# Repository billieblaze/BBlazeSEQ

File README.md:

BBlaze-SEQ
==========

Arduino Based Midi Sequencer w/ LCD, Nav Buttons, RGB LED Matrix / Keypad

This is my first Arduino Project, but not my first microcontroller project.   

Platform: 
=========

* SainSmart Arduino Mega 2560 clone
* SainSmart i2c LCD
* MIDI IN / MIDI OUT (6n139)
* MicroChip 24LC256 - 256k RAM 
* SparkFun 4x4 RGB LED / Button Matrix - 74hc595 shift registers for LED - 74hc164/165 for button matrix

* Navigation 
    - using a digital in module from Midibox.org - but again, just some 74hc595
    * 8 rotary encoder / swithces 
    * 5 nav buttons
    * pattern change rotary/encoder

Libraries:
==========

* SainSmart i2c LCD
* ShiftMatrixPWM
* MIDI 
* Timer3 

Roadmap: 
========

* add save / clear / copy pattern
* allow CC data in the pattern
* PCB Design

ChangeLog:
==========

* v0.9 - Split core .ino file into packages (lcd, keypad, matrix, etc) - working on timing (might remove interrupt) and general cleanup of UI handlers
* v0.8 - Added 24LC256 - working on timing of UI routines - added "record+keyboard" mode
* v0.7 - moved the button handling to an interrupt and added "updateLCD" flag which will update on the next loop()
* v0.6 - switch to i2c LCD and arduino mega 2560
* v0.5 - Replace sequence array that come from Cahors / buttons now toggle notes in the array
* v0.4 - Integrate Keypad w/ a Voltage Divider to A5
* v0.3 - Integrate LED Matrix (shiftPWMMatrix + 75hc595)
* v0.2 - LCD / Menu / Nav Buttons / Simple OS   (sainSmart LCD / Keypad)
* v0.1 - basic poc / find libraries

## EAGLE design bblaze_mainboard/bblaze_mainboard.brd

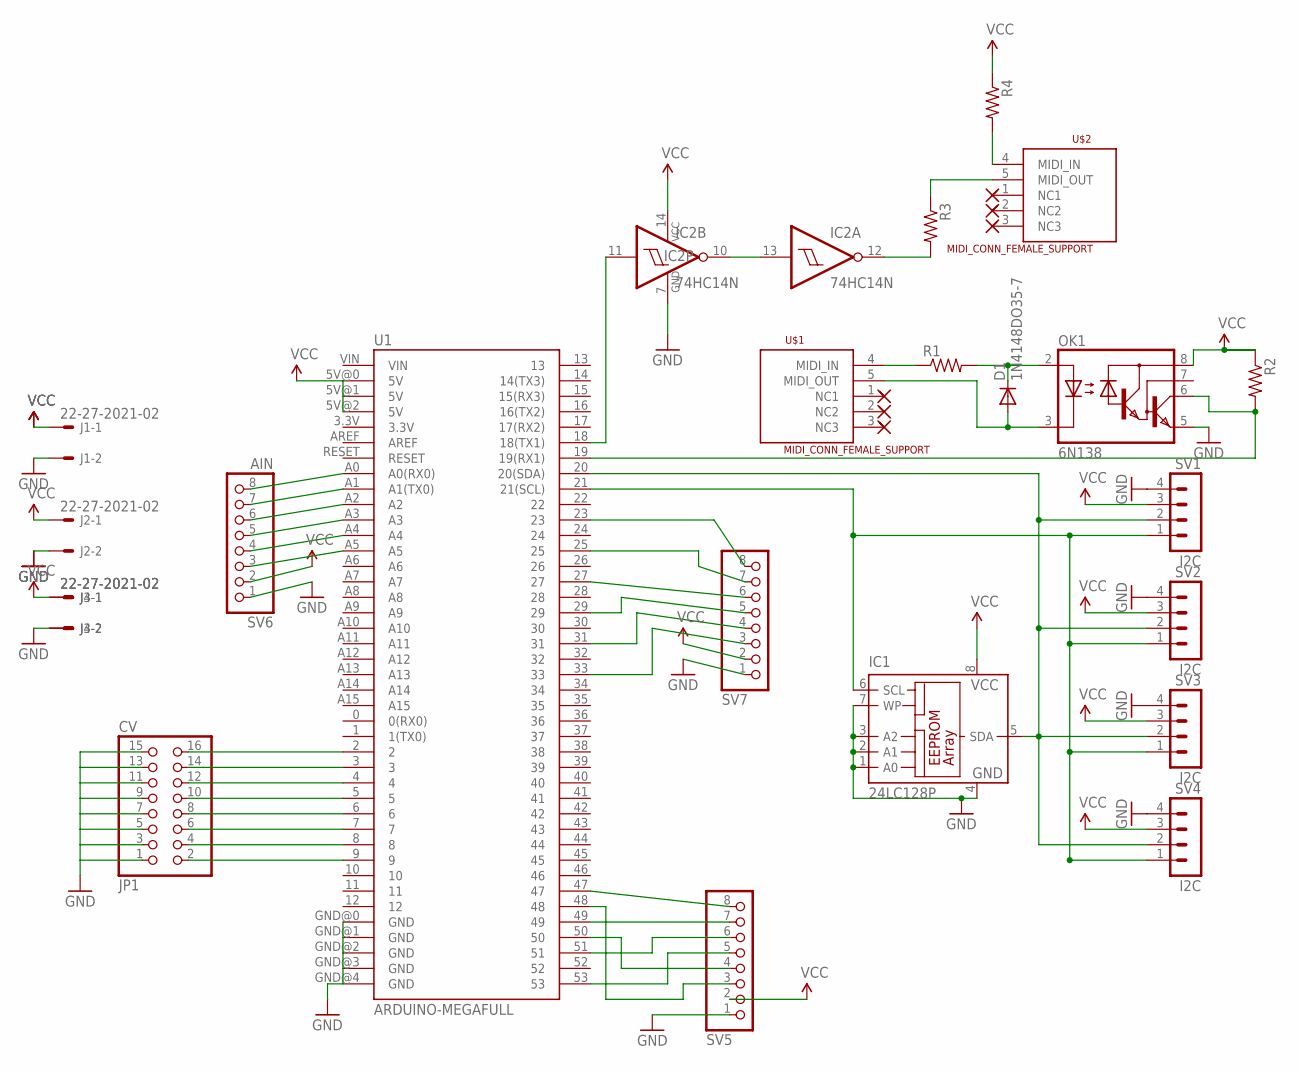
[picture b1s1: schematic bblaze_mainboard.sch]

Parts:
D1: 1N4148DO35-7; DO35-7
IC1: 24LC128P; DIL8
IC2: 74HC14N; DIL14
J1, J2, J3, J4: 22-27-2021-02; 6410-02
JP1: CV; 2X08
OK1: 6N138; DIL08
R1, R2, R3, R4: RESISTORKIT; AXIAL-0.3-KIT
SV1, SV2, SV3, SV4: I2C; MA04-1
SV5, SV7: PINHD-1X8; 1X08
SV6: AIN; 1X08
U1: ARDUINO-MEGAFULL; ARDUINO_MEGA
U$1, U$2: MIDI_CONN_FEMALE_SUPPORT; DIN_5_FEMALE_SUPPORT

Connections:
GND: IC1.1 (A0), IC1.2 (A1), IC1.3 (A2), IC1.4 (GND), IC1.7 (WP), IC2.7 (GND), J1.2, J2.2, J3.2, J4.2, JP1.1, JP1.3, JP1.5, JP1.7, JP1.9, JP1.11, JP1.13, JP1.15, OK1.5 (GND), SV1.4, SV2.4, SV3.4, SV4.4, SV5.1, SV6.1, SV7.1, U1.GND@0 (GND), U1.GND@1 (GND), U1.GND@2 (GND), U1.GND@3 (GND), U1.GND@4 (GND)
unnamed: D1.C, OK1.2 (A), R1.P$2 (2)
unnamed: D1.A, OK1.3 (C), U$1.5 (MIDI_OUT)
unnamed: R1.P$1 (1), U$1.4 (MIDI_IN)
unnamed: JP1.16, U1.2
unnamed: OK1.8 (VCC), R2.P$1 (1)
unnamed: OK1.6 (VO), R2.P$2 (2), U1.19 (19(RX1))
unnamed: JP1.14, U1.3
unnamed: IC1.5 (SDA), SV1.2, SV2.2, SV3.2, SV4.2, U1.20 (20(SDA))
unnamed: IC1.6 (SCL), SV1.1, SV2.1, SV3.1, SV4.1, U1.21 (21(SCL))
unnamed: JP1.12, U1.4
unnamed: JP1.10, U1.5
unnamed: JP1.8, U1.6
unnamed: JP1.6, U1.7
unnamed: JP1.4, U1.8
unnamed: JP1.2, U1.9
unnamed: SV5.5, U1.53
unnamed: SV5.6, U1.51
unnamed: SV5.4, U1.50
unnamed: SV5.3, U1.48
unnamed: SV5.8, U1.47
unnamed: IC2.11 (I), U1.18 (18(TX1))
unnamed: IC2.10 (O), IC2.13 (I)
unnamed: IC2.12 (O), R3.P$2 (2)
unnamed: R3.P$1 (1), U$2.5 (MIDI_OUT)
unnamed: R4.P$2 (2), U$2.4 (MIDI_IN)
unnamed: SV6.8, U1.A0 (A0(RX0))
unnamed: SV6.7, U1.A1 (A1(TX0))
unnamed: SV6.6, U1.A2
unnamed: SV6.5, U1.A3
unnamed: SV6.4, U1.A4
unnamed: SV6.3, U1.A5
unnamed: SV7.8, U1.23
unnamed: SV7.7, U1.25
unnamed: SV7.6, U1.27
unnamed: SV7.5, U1.29
unnamed: SV7.4, U1.31
unnamed: SV7.3, U1.33
unnamed: SV5.7, U1.49
VCC: IC1.8 (VCC), IC2.14 (VCC), J1.1, J2.1, J3.1, J4.1, R4.P$1 (1), SV1.3, SV2.3, SV3.3, SV4.3, SV5.2, SV6.2, SV7.2, U1.5V@0 (5V), U1.5V@1 (5V), U1.5V@2 (5V)

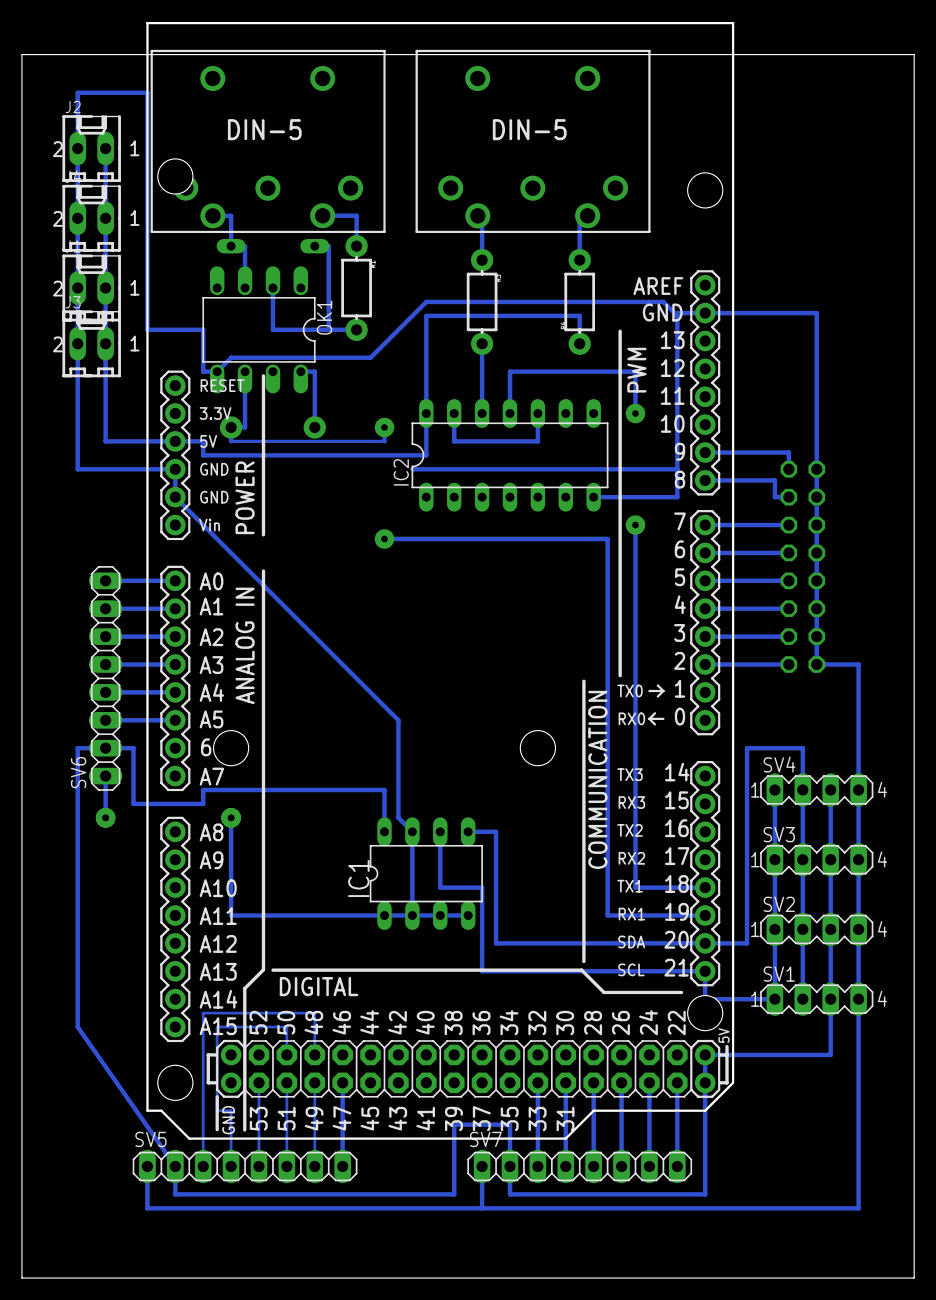
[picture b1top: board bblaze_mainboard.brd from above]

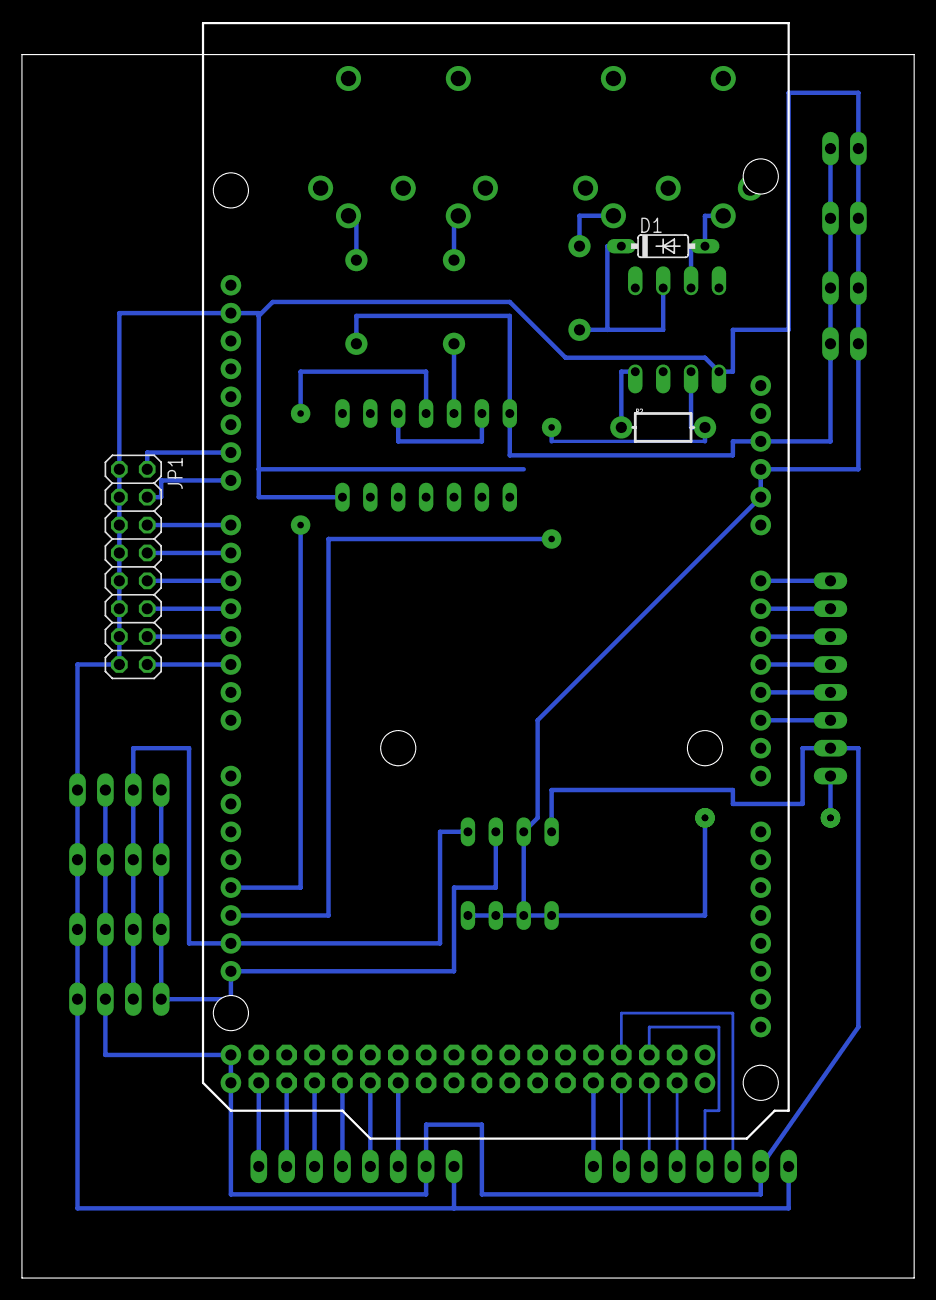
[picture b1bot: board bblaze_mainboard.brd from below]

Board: 2 copper layers, 81.1 x 114.2 mm, 23 parts (3 on the bottom side), 40 nets.

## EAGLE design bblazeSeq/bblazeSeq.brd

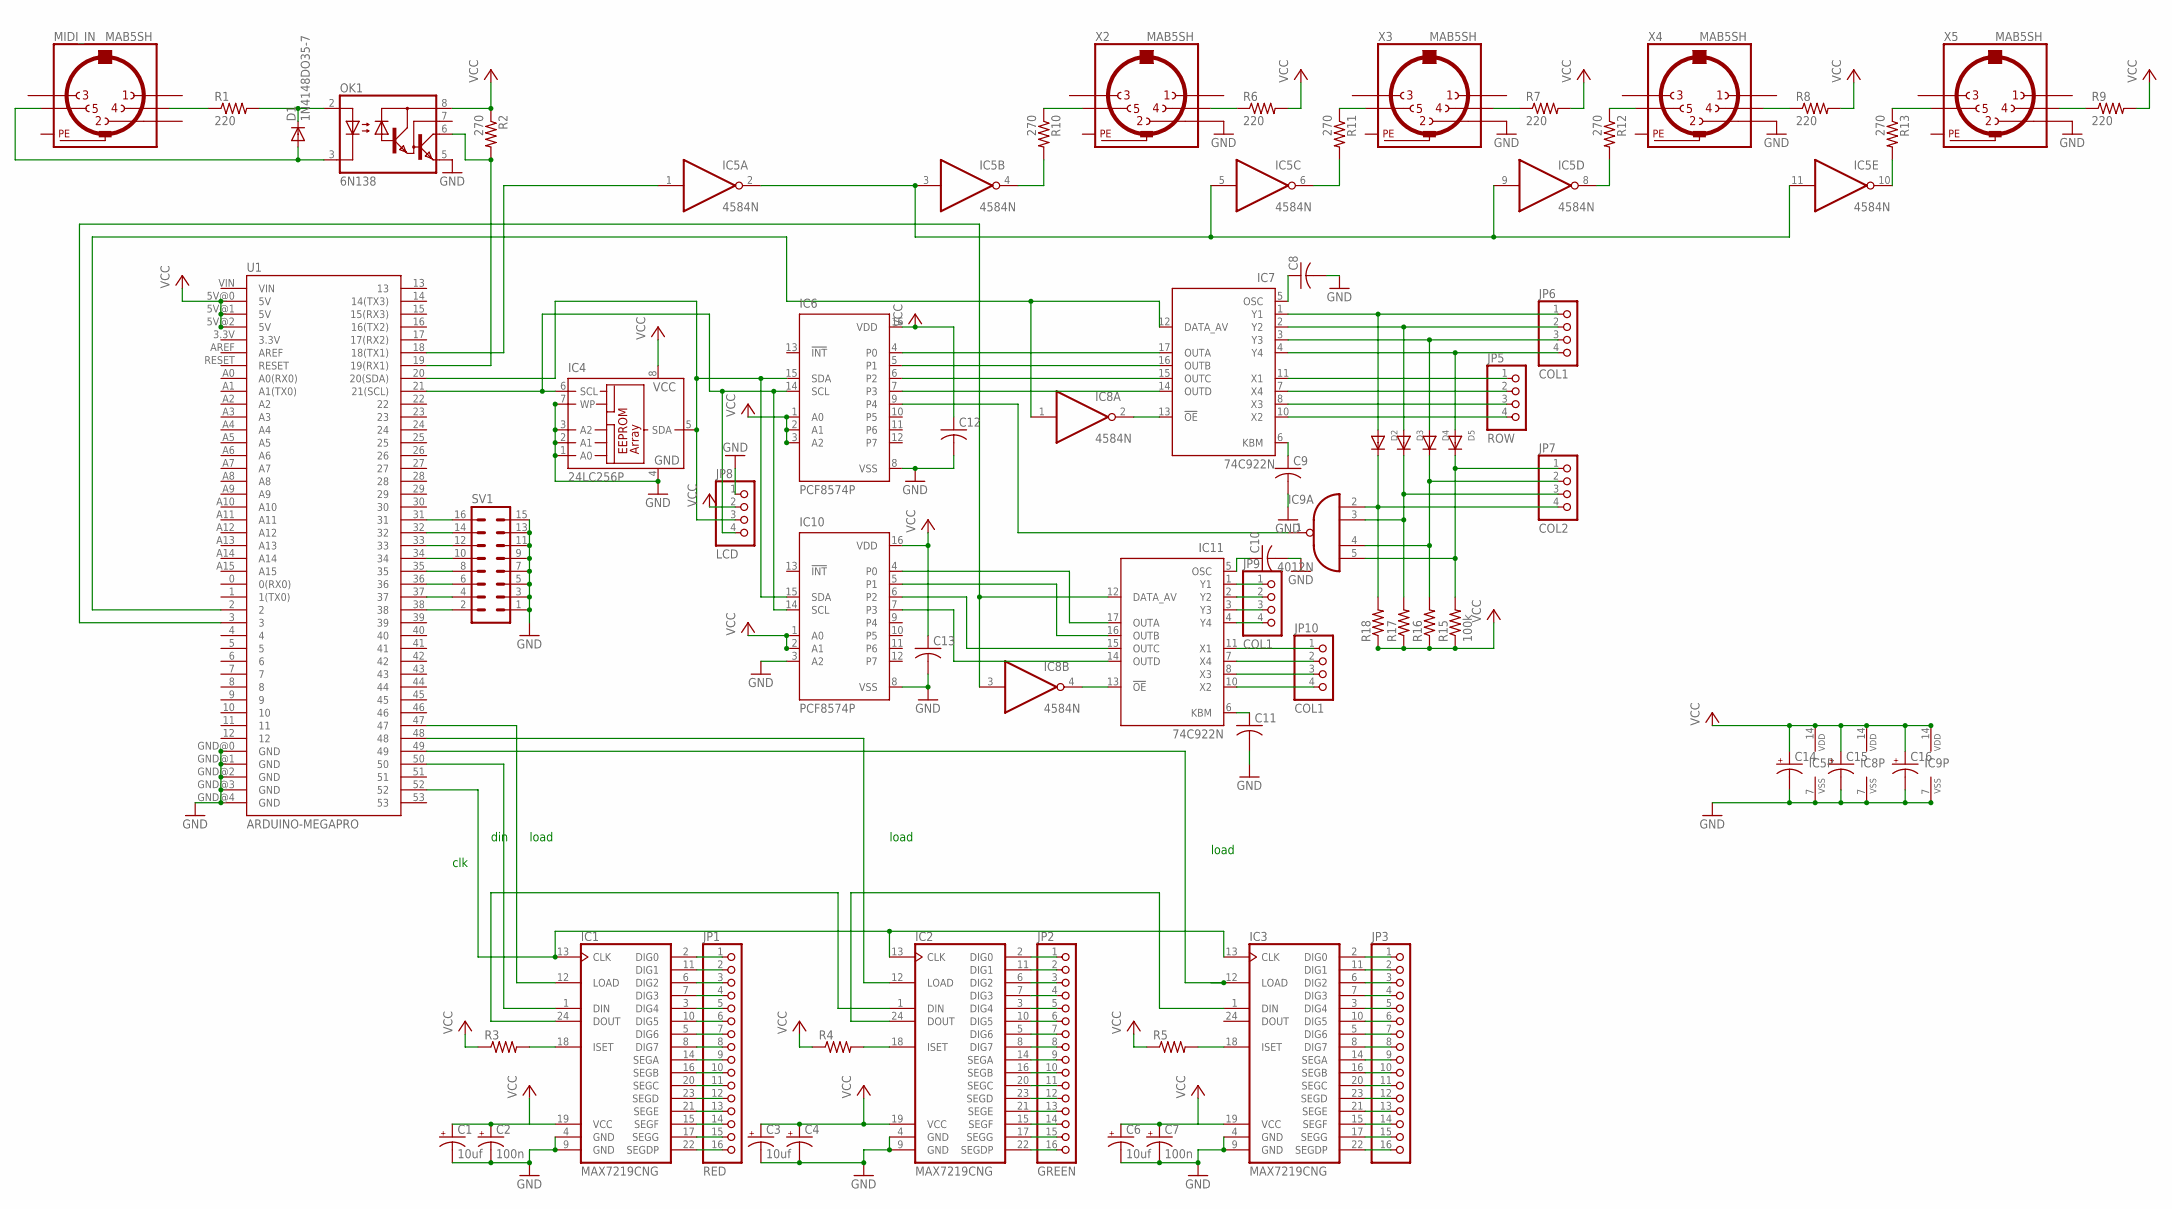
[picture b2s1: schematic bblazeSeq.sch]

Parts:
C1, C3, C6: 10uf; E2,5-6E
C2, C7: 100n; E2,5-6E
C4, C14, C15, C16: CPOL-USE2,5-6E; E2,5-6E
C8, C9, C10, C11, C12, C13: C-US050-024X044; C050-024X044
D1: 1N4148DO35-7; DO35-7
D2, D3, D4, D5: DIODEDO-1N4148; DO-1N4148
IC1, IC2, IC3: MAX7219CNG; DIL24-3
IC4: 24LC256P; DIL8
IC5, IC8: 4584N; DIL14
IC6, IC10: PCF8574P; DIL16
IC7, IC11: 74C922N; DIL18
IC9: 4012N; DIL14
JP1: RED; 1X16
JP2: GREEN; 1X16
JP3: PINHD-1X16; 1X16
JP5: ROW; 1X04
JP6, JP9, JP10: COL1; 1X04
JP7: COL2; 1X04
JP8: LCD; 1X04
MIDI_IN: MAB5SH
OK1: 6N138; DIL08
R1: 220; 0207/10
R2, R10, R11, R12, R13: 270; 0207/10
R3, R4, R5, R16, R17, R18: R-US_0204/7; 0204/7
R6, R7, R8, R9: 220; 0204/7
R15: 100k; 0204/7
SV1: MA08-2
U1: ARDUINO-MEGAPRO; ARDUINO_MEGA-PRO-3.3V
X2, X3, X4, X5: MAB5SH

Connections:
GND: C1.-, C2.-, C3.-, C4.-, C6.-, C7.-, C8.2, C9.2, C10.2, C11.2, C12.2, C13.2, C14.-, C15.-, C16.-, IC1.4 (GND), IC1.9 (GND), IC2.4 (GND), IC2.9 (GND), IC3.4 (GND), IC3.9 (GND), IC4.1 (A0), IC4.2 (A1), IC4.3 (A2), IC4.4 (GND), IC4.7 (WP), IC5.7 (VSS), IC6.8 (VSS), IC7.9 (GND), IC8.7 (VSS), IC9.7 (VSS), IC10.3 (A2), IC10.8 (VSS), IC11.9 (GND), JP8.1, OK1.5 (GND), SV1.1, SV1.3, SV1.5, SV1.7, SV1.9, SV1.11, SV1.13, SV1.15, U1.GND@0 (GND), U1.GND@1 (GND), U1.GND@2 (GND), U1.GND@3 (GND), U1.GND@4 (GND), X2.2, X3.2, X4.2, X5.2
unnamed: IC6.9 (P4), IC9.1 (O)
unnamed: D2.C, IC9.2 (I0), JP7.4, R18.2
unnamed: D3.C, IC9.3 (I1), JP7.3, R17.2
unnamed: D4.C, IC9.4 (I2), JP7.2, R16.2
unnamed: D5.C, IC9.5 (I3), JP7.1, R15.2
unnamed: IC3.2 (DIG0), JP3.1
unnamed: IC3.11 (DIG1), JP3.2
unnamed: IC3.6 (DIG2), JP3.3
unnamed: IC3.7 (DIG3), JP3.4
unnamed: IC3.3 (DIG4), JP3.5
unnamed: IC3.10 (DIG5), JP3.6
unnamed: IC3.5 (DIG6), JP3.7
unnamed: IC3.8 (DIG7), JP3.8
unnamed: IC3.14 (SEGA), JP3.9
unnamed: D1.A, MIDI_IN.5, OK1.3 (C)
unnamed: D1.C, OK1.2 (A), R1.2
unnamed: MIDI_IN.4, R1.1
unnamed: OK1.6 (VO), R2.2, U1.19 (19(RX1))
unnamed: IC1.18 (ISET), R3.2
unnamed: IC4.6 (SCL), IC6.14 (SCL), IC10.14 (SCL), JP8.4, U1.21 (21(SCL))
unnamed: IC4.5 (SDA), IC6.15 (SDA), IC10.15 (SDA), JP8.3, U1.20 (20(SDA))
unnamed: IC2.18 (ISET), R4.2
unnamed: IC3.18 (ISET), R5.2
unnamed: IC3.12 (LOAD), U1.49
unnamed: IC2.12 (LOAD), U1.48
unnamed: C1.+, C2.+, IC1.19 (VCC)
unnamed: IC5.1 (I), U1.18 (18(TX1))
unnamed: C6.+, C7.+, IC3.19 (VCC)
unnamed: IC2.24 (DOUT), IC3.1 (DIN)
unnamed: IC1.24 (DOUT), IC2.1 (DIN)
unnamed: IC1.13 (CLK), IC2.13 (CLK), IC3.13 (CLK), U1.52
unnamed: R6.1, X2.4
unnamed: IC1.1 (DIN), U1.50
unnamed: IC1.12 (LOAD), U1.47
unnamed: R7.1, X3.4
unnamed: R8.1, X4.4
unnamed: R9.1, X5.4
unnamed: R10.1, X2.5
unnamed: R11.1, X3.5
unnamed: R12.1, X4.5
unnamed: R13.1, X5.5
unnamed: IC5.4 (O), R10.2
unnamed: IC5.6 (O), R11.2
unnamed: IC5.8 (O), R12.2
unnamed: IC5.10 (O), R13.2
unnamed: IC5.2 (O), IC5.3 (I), IC5.5 (I), IC5.9 (I), IC5.11 (I)
unnamed: IC7.12 (DATA_AV), IC8.1 (I), U1.2
unnamed: IC6.4 (P0), IC7.17 (OUTA)
unnamed: IC6.5 (P1), IC7.16 (OUTB)
unnamed: IC6.6 (P2), IC7.15 (OUTC)
unnamed: IC6.7 (P3), IC7.14 (OUTD)
unnamed: C9.1, IC7.6 (KBM)
unnamed: C8.1, IC7.5 (OSC)
unnamed: IC7.13 (!OE), IC8.2 (O)
unnamed: IC7.11 (X1), JP5.1
unnamed: IC7.7 (X4), JP5.2
unnamed: IC7.8 (X3), JP5.3
unnamed: IC7.10 (X2), JP5.4
unnamed: D2.A, IC7.1 (Y1), JP6.1
unnamed: D3.A, IC7.2 (Y2), JP6.2
unnamed: D4.A, IC7.3 (Y3), JP6.3
unnamed: D5.A, IC7.4 (Y4), JP6.4
unnamed: IC3.16 (SEGB), JP3.10
unnamed: IC3.20 (SEGC), JP3.11
unnamed: IC3.23 (SEGD), JP3.12
unnamed: IC3.21 (SEGE), JP3.13
unnamed: IC3.15 (SEGF), JP3.14
unnamed: IC3.17 (SEGG), JP3.15
unnamed: IC3.22 (SEGDP), JP3.16
unnamed: IC1.2 (DIG0), JP1.1
unnamed: IC1.11 (DIG1), JP1.2
unnamed: IC1.6 (DIG2), JP1.3
unnamed: IC1.7 (DIG3), JP1.4
unnamed: IC1.3 (DIG4), JP1.5
unnamed: IC1.10 (DIG5), JP1.6
unnamed: IC1.5 (DIG6), JP1.7
unnamed: IC1.8 (DIG7), JP1.8
unnamed: IC1.14 (SEGA), JP1.9
unnamed: IC1.16 (SEGB), JP1.10
unnamed: IC1.20 (SEGC), JP1.11
unnamed: IC1.23 (SEGD), JP1.12
unnamed: IC1.21 (SEGE), JP1.13
unnamed: IC1.15 (SEGF), JP1.14
unnamed: IC1.17 (SEGG), JP1.15
unnamed: IC1.22 (SEGDP), JP1.16
unnamed: IC2.2 (DIG0), JP2.1
unnamed: IC2.11 (DIG1), JP2.2
unnamed: IC2.6 (DIG2), JP2.3
unnamed: IC2.7 (DIG3), JP2.4
unnamed: IC2.3 (DIG4), JP2.5
unnamed: IC2.10 (DIG5), JP2.6
unnamed: IC2.5 (DIG6), JP2.7
unnamed: IC2.8 (DIG7), JP2.8
unnamed: IC2.14 (SEGA), JP2.9
unnamed: IC2.16 (SEGB), JP2.10
unnamed: IC2.20 (SEGC), JP2.11
unnamed: IC2.23 (SEGD), JP2.12
unnamed: IC2.21 (SEGE), JP2.13
unnamed: IC2.15 (SEGF), JP2.14
unnamed: IC2.17 (SEGG), JP2.15
unnamed: IC2.22 (SEGDP), JP2.16
unnamed: IC8.4 (O), IC11.13 (!OE)
unnamed: IC8.3 (I), IC11.12 (DATA_AV), U1.3
unnamed: IC10.4 (P0), IC11.17 (OUTA)
unnamed: IC10.5 (P1), IC11.16 (OUTB)
unnamed: IC10.6 (P2), IC11.15 (OUTC)
unnamed: IC10.7 (P3), IC11.14 (OUTD)
unnamed: C10.1, IC11.5 (OSC)
unnamed: C11.1, IC11.6 (KBM)
unnamed: IC11.1 (Y1), JP9.1
unnamed: IC11.2 (Y2), JP9.2
unnamed: IC11.3 (Y3), JP9.3
unnamed: IC11.4 (Y4), JP9.4
unnamed: IC11.11 (X1), JP10.1
unnamed: IC11.7 (X4), JP10.2
unnamed: IC11.8 (X3), JP10.3
unnamed: IC11.10 (X2), JP10.4
unnamed: SV1.16, U1.31
unnamed: SV1.14, U1.32
unnamed: SV1.12, U1.33
unnamed: SV1.10, U1.34
unnamed: SV1.8, U1.35
unnamed: SV1.6, U1.36
unnamed: SV1.4, U1.37
unnamed: SV1.2, U1.38
PE: MIDI_IN.PE, MIDI_IN.PE@ (PE), X2.PE, X2.PE@ (PE), X3.PE, X3.PE@ (PE), X4.PE, X4.PE@ (PE), X5.PE, X5.PE@ (PE)
VCC: C3.+, C4.+, C12.1, C13.1, C14.+, C15.+, C16.+, IC2.19 (VCC), IC4.8 (VCC), IC5.14 (VDD), IC6.1 (A0), IC6.2 (A1), IC6.3 (A2), IC6.16 (VDD), IC7.18 (VCC), IC8.14 (VDD), IC9.14 (VDD), IC10.1 (A0), IC10.2 (A1), IC10.16 (VDD), IC11.18 (VCC), JP8.2, OK1.8 (VCC), R2.1, R3.1, R4.1, R5.1, R6.2, R7.2, R8.2, R9.2, R15.1, R16.1, R17.1, R18.1, U1.5V@0 (5V), U1.5V@1 (5V), U1.5V@2 (5V)

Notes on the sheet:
clk
din
load

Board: 2 copper layers, 65 parts (0 on the bottom side), 128 nets, no tracks yet.

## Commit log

2012-05-02 initial checkin of v0.3
2012-05-02 lol, arduino wouldn't take a - in the sketch name!
2012-05-03 fixes to nav keypad after introducing shiftMatrixPWM LED Matrix scanning is synced to the main loop now..
2012-05-06 stripped back song format - used voltage divider and analog pin to POC the keypad integration
2012-05-08 replaced the sequence array from cahors with a simpler one to help understand how to manipulate / traverse the data..
2012-05-08 removed util.h which came from cahors
2012-05-08 adjusted timing / note + velocity arrays..
2012-05-16 split up config - added keypad decoder - added another button pad
2012-06-30 update to v0.8 - see changelog
2012-07-03 split core into packages - working on timing and cleaning up UI handlers
2012-07-03 fix keypad polling issues after refactoring the interrupt / service routine
2012-07-03 touched up ui service routines - implemented control knobs
2012-07-05 Added test sketches which have been used to verify different stages of the hardware design
2012-07-26 worked on rotary encoders quite a bit - still a little flaky, but getting better
2012-07-27 trying to squeeze some more speed out of the UI - a long way to go, but getting there
2012-07-31 more ui tweaking for speed..
2012-08-03 more speed in lcd / ui - reduced shiftmatrixpwm brightness to 1
2012-08-10 fixes to keypad scanning..
    was not shifting in right and was missing 2 bits.. maybe ditch the
    shiftOuts since i'm on Mega now?
2012-09-11 fixed glitch in keypad
2012-09-11 Added GATE to each channel
2012-09-25 added more midi.read to prevent timing glitches and found a misplaced updateMatrix which was causing matrix refresh every loop
2012-11-17 speed + triggers
    added 8 triggers and more calls to midi.read
2013-06-25 test eclipse git
2013-06-25 test2
2013-08-14 add initial eagle files
2013-10-07 1/2 working in chibios
    i've got the DIN stuff working, and am trying to get the lcd going..
    consolidating some of the files so i can later abstract different types
    of DIN classes
2013-10-09 more work on chibios.. got the lcd partly back, working on the matrix next
2013-10-09 messin with tests

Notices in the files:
parts and their libraries:
SparkFun-Boards: Licensing: CC v3.0 Share-Alike You are welcome to use this library for commercial purposes.
